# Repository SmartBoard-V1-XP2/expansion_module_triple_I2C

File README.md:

# Expansion odule : Triple I2C

The Triple I2C Expansion Module is a practical addition for Smartboard users, facilitating smart prototyping by enabling the management of multiple I2C devices. This module is designed to easily integrate with single connectors on the Smartboard, offering three independent I2C outputs.

## Key Features and Functions

- **Three Independent I2C Outputs**: Allows the connection of multiple I2C devices, even with overlapping address ranges.
- **Versatile Connectivity**: Features connectors for both JST and GROVE, as well as GOLD PIN headers, making it easy to connect an oscilloscope for bus monitoring.
- **Application Flexibility**: Ideal for connecting sensors, memory modules, Real-Time Clocks (RTC), and other I2C compatible devices.
- **Educational Tool**: Serves as an excellent resource for learning about creating IP modules, particularly in the context of hardware I2C interfaces.

## Hardware and Design

## Contributions and Feedback
Contributions to this project are welcome. If you have suggestions for improvement or have developed additional features, please fork the repository, make your changes, and submit a pull request. For any questions or issues, please open an issue in the GitHub repository.

## License
This charger project is licensed under the MIT License with the following terms:

- **Permission to Use**: You are free to use, modify, and distribute this charger design in both private and commercial settings.
- **Attribution Requirement**: While not required, attribution to the original author, Adam Łuczak, is appreciated. This can be done through a citation or a link back to this repository.
- **No Warranty**: This design is provided "as is", without warranty of any kind. Use it at your own risk.
- **Liability**: The author is not liable for any damages or losses that may arise from the use of this design.

For the full terms and conditions, please refer to the MIT License documentation.

## Contact
Should you have any inquiries or suggestions regarding this charger project, please don't hesitate to contact Adam Łuczak at adam.luczak@outlook.com.

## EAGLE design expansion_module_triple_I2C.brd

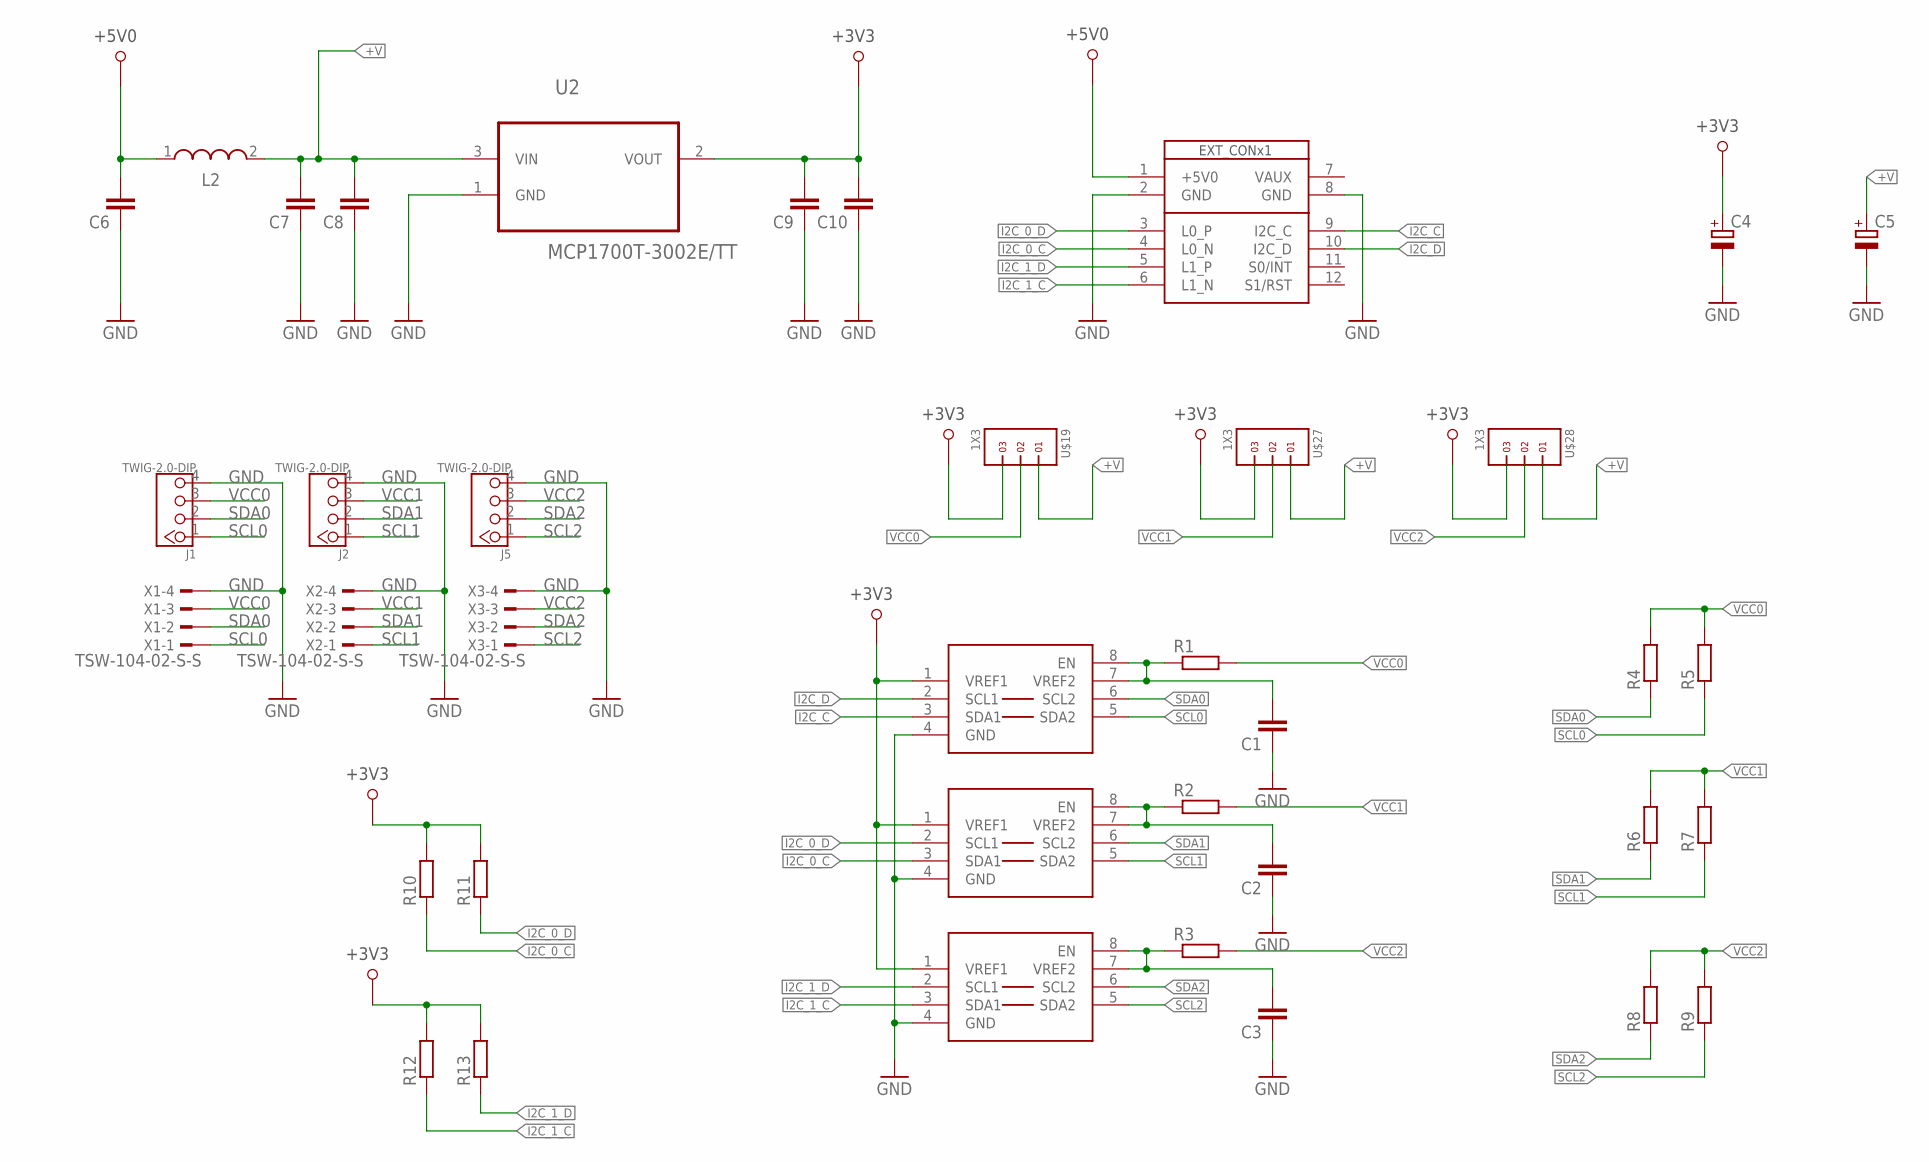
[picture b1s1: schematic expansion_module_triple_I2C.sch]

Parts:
C1, C2, C3, C6, C7, C8, C9, C10: C-EUC0603; C0603
C4, C5: CPOL-EUSMCB; SMC_B
J1, J2, J5: TWIG-2.0-DIP; 2.0_1X4
L2: WE-LQ_1210; WE-LQ_M
R1, R2, R3, R4, R5, R6, R7, R8, R9, R10, R11, R12, R13: R-EU_R0603; R0603
U2: MCP1700T-3002E/TT; SOT95P237X112-3N
U$2: SB_EXT_CON_X1; SB_EXT_CON_X1_FULL
U$16, U$20, U$31: PCA9306; PSOP-8
U$19, U$27, U$28: 1X3
X1, X2, X3: TSW-104-02-S-S

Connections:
+3V3: C4.+, C9.2, C10.2, R10.2, R11.2, R12.2, R13.2, U2.2 (VOUT), U$16.1 (VREF1), U$19.3, U$20.1 (VREF1), U$27.3, U$28.3, U$31.1 (VREF1)
+5V0: C6.2, L2.1, U$2.1 (+5V0)
+V: C5.+, C7.2, C8.2, L2.2, U2.3 (VIN), U$19.1, U$27.1, U$28.1
GND: C1.1, C2.1, C3.1, C4.-, C5.-, C6.1, C7.1, C8.1, C9.1, C10.1, J1.4, J2.4, J5.4, U2.1 (GND), U$2.2 (GND), U$2.8 (GND), U$16.4 (GND), U$20.4 (GND), U$31.4 (GND), X1.4, X2.4, X3.4
I2C_0_C: R10.1, U$2.4 (L0_N), U$20.3 (SDA1)
I2C_0_D: R11.1, U$2.3 (L0_P), U$20.2 (SCL1)
I2C_1_C: R12.1, U$2.6 (L1_N), U$31.3 (SDA1)
I2C_1_D: R13.1, U$2.5 (L1_P), U$31.2 (SCL1)
I2C_C: U$2.9 (I2C_C), U$16.3 (SDA1)
I2C_D: U$2.10 (I2C_D), U$16.2 (SCL1)
unnamed: C1.2, R1.1, U$16.7 (VREF2), U$16.8 (EN)
unnamed: C2.2, R2.1, U$20.7 (VREF2), U$20.8 (EN)
unnamed: C3.2, R3.1, U$31.7 (VREF2), U$31.8 (EN)
SCL0: J1.1, R5.1, U$16.5 (SDA2), X1.1
SCL1: J2.1, R7.1, U$20.5 (SDA2), X2.1
SCL2: J5.1, R9.1, U$31.5 (SDA2), X3.1
SDA0: J1.2, R4.1, U$16.6 (SCL2), X1.2
SDA1: J2.2, R6.1, U$20.6 (SCL2), X2.2
SDA2: J5.2, R8.1, U$31.6 (SCL2), X3.2
VCC0: J1.3, R1.2, R4.2, R5.2, U$19.2, X1.3
VCC1: J2.3, R2.2, R6.2, R7.2, U$27.2, X2.3
VCC2: J5.3, R3.2, R8.2, R9.2, U$28.2, X3.3

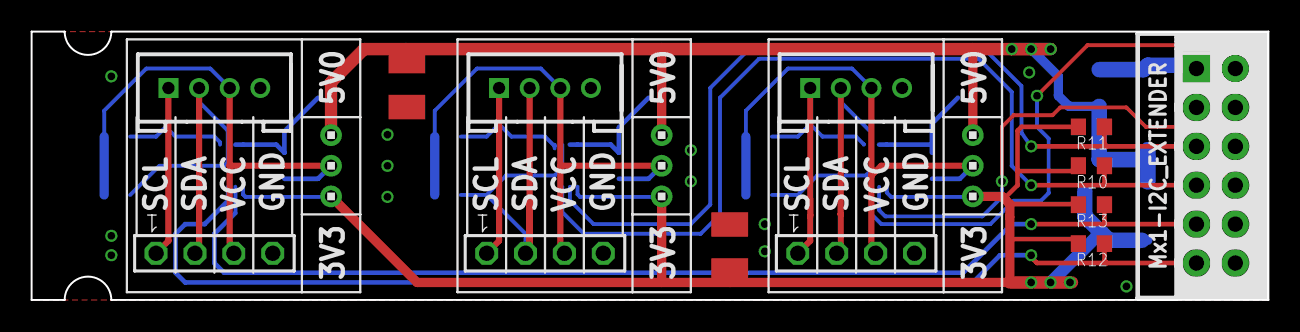
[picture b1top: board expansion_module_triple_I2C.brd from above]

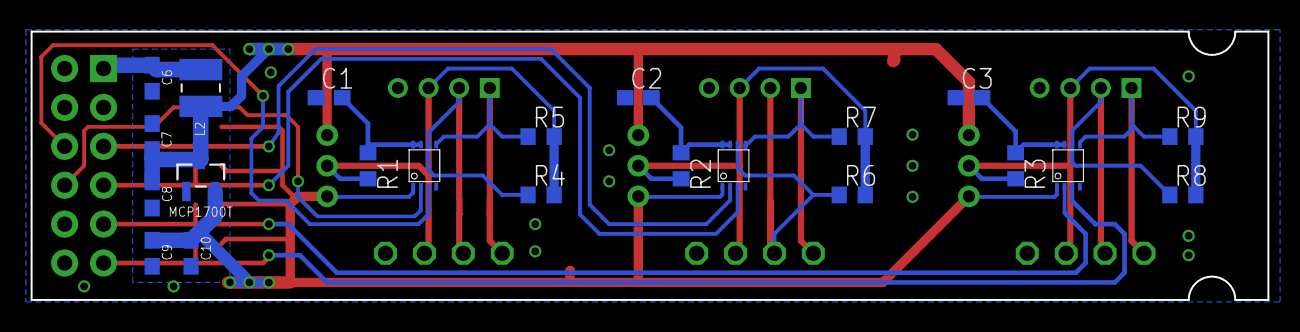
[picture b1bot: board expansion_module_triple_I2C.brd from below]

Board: 2 copper layers, 80.8 x 17.5 mm, 38 parts (22 on the bottom side), 22 nets.

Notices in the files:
README.md:
License: MIT
parts and their libraries:
EagleLibrary_Wuerth_Elektronik_eiSos_rev: Copyright: Würth Elektronik
SparkFun-DigitalIC: Licensing: CC v3.0 Share-Alike You are welcome to use this library for commercial purposes.
